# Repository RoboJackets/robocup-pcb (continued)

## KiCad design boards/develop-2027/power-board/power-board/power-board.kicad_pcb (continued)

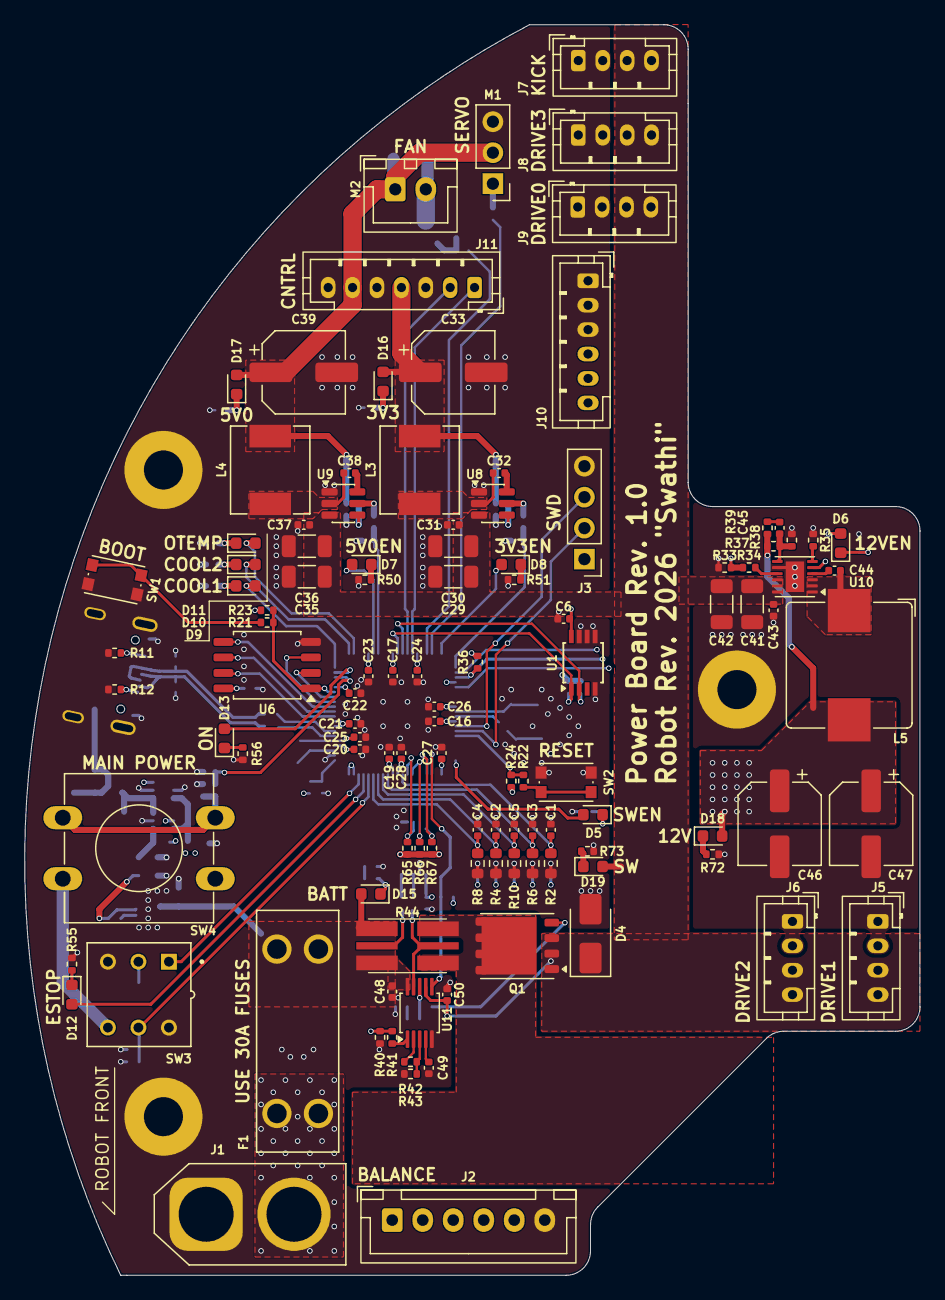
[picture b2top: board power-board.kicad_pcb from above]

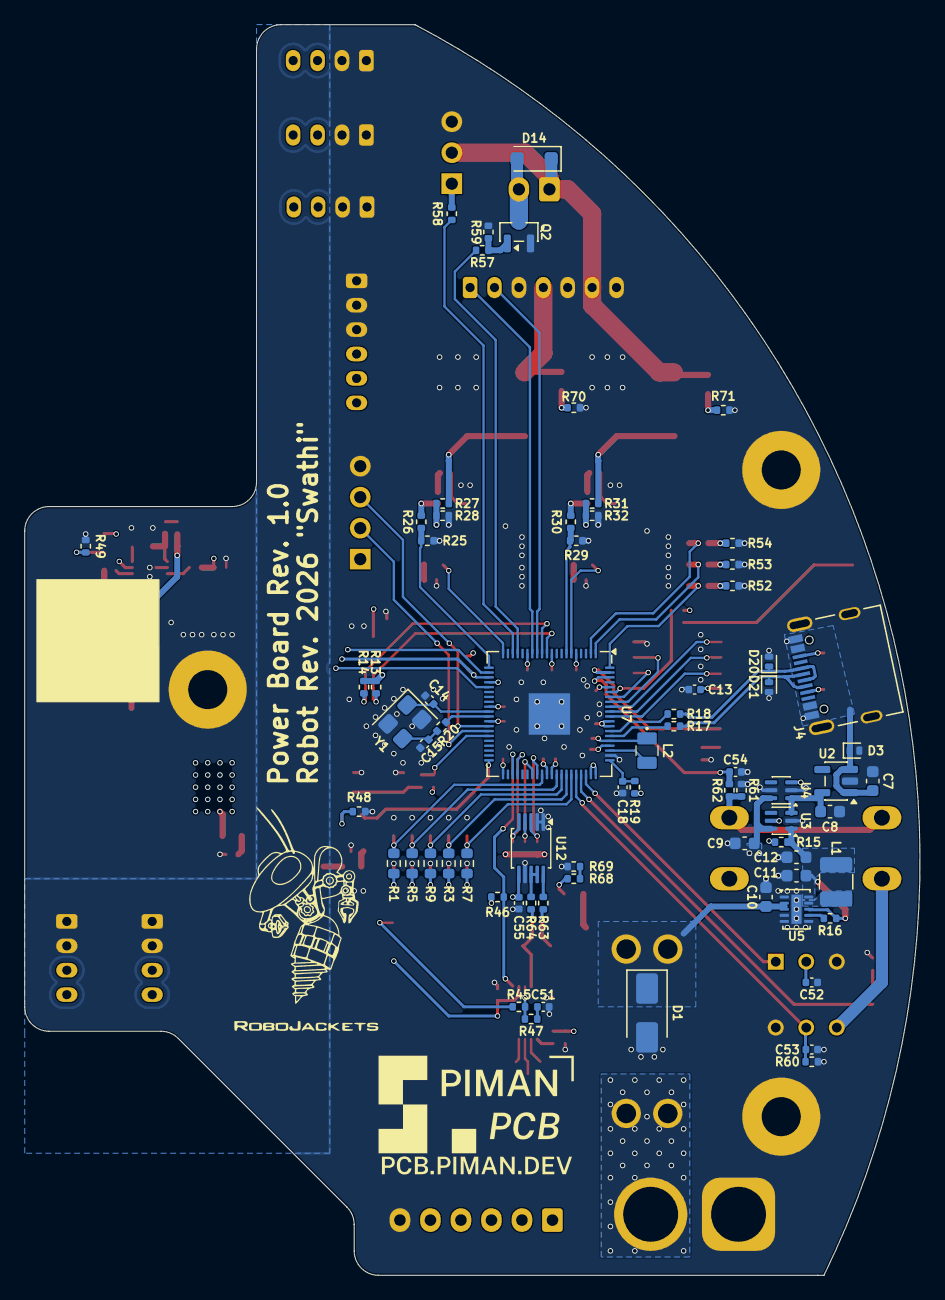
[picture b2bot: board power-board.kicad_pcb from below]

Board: 4 copper layers, 73.4 x 102.5 mm, 187 parts (72 on the bottom side), 119 nets.

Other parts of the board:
C6: 100n; C_0402_1005Metric
C48, C50: 100n 50V; C_0402_1005Metric
C49: 1n; C_0402_1005Metric
C51: 10n; C_0402_1005Metric
D4: SMAJ22CA; D_SMA
D19: KT-0603G; LED_0603_1608Metric
Q1: BSC014N06NS; Infineon_PG-TDSON-8_6.15x5.15mm
R13, R14, R73: 4.7k; R_0402_1005Metric
R40, R46: 100k; R_0402_1005Metric
R41, R47: 1k; R_0402_1005Metric
R42: 41.2k; R_0402_1005Metric
R43: 5.23k; R_0402_1005Metric
R44: 1.5m ± 1% 2W; R_Shunt_Analog_2512_6332_HighAccuracy
R45: 10; R_0402_1005Metric
U1: LM75ADP; TSSOP-8_3x3mm_P0.65mm
U11: TPS2491DGS; TSSOP-10_3x3mm_P0.5mm

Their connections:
+3.3V: C6.1, R13.1, R14.1, R46.1, U1.8 (VCC); also elsewhere on the board
/Battery Connectors/VBATT: C48.1, R44.4, U11.10 (VCC); also elsewhere on the board
/MCU/SCL0: R14.2, U1.2 (SCL); also elsewhere on the board
/MCU/SDA0: R13.2, U1.1 (SDA); also elsewhere on the board
/MCU/SW_OK: R46.2, U11.6 (PG); also elsewhere on the board
/Output Power Stage/25V, 30A Load Switch/SHUNT_H: R44.3; also elsewhere on the board
/Output Power Stage/25V, 30A Load Switch/SHUNT_L: R44.2, U11.9 (SENSE); also elsewhere on the board
/Output Power Stage/LOADSW_EN: R40.1, R41.2; also elsewhere on the board
GND: C6.2, C48.2, C49.2, C50.2, C51.2, D4.2 (A2), R40.2, R43.2, R73.2, U1.4 (GND), U1.5 (A2), U1.6 (A1), U1.7 (A0), U11.5 (GND); also elsewhere on the board
unnamed: C51.1, R47.2
unnamed: D19.1 (K), R73.1
unnamed: Q1.5 (D), R44.1
unnamed: Q1.4 (G), R45.1
unnamed: R41.1, U11.1 (EN)
unnamed: R45.2, R47.1, U11.8 (GATE)
unnamed: R42.2, R43.1, U11.3 (PROG)
unnamed: C49.1, U11.4 (TIMER)
unnamed: R42.1, U11.2 (VREF)
VIN: C50.1, D4.1 (A1), D19.2 (A), Q1.1 (S), Q1.2 (S), Q1.3 (S), U11.7 (OUT); also elsewhere on the board

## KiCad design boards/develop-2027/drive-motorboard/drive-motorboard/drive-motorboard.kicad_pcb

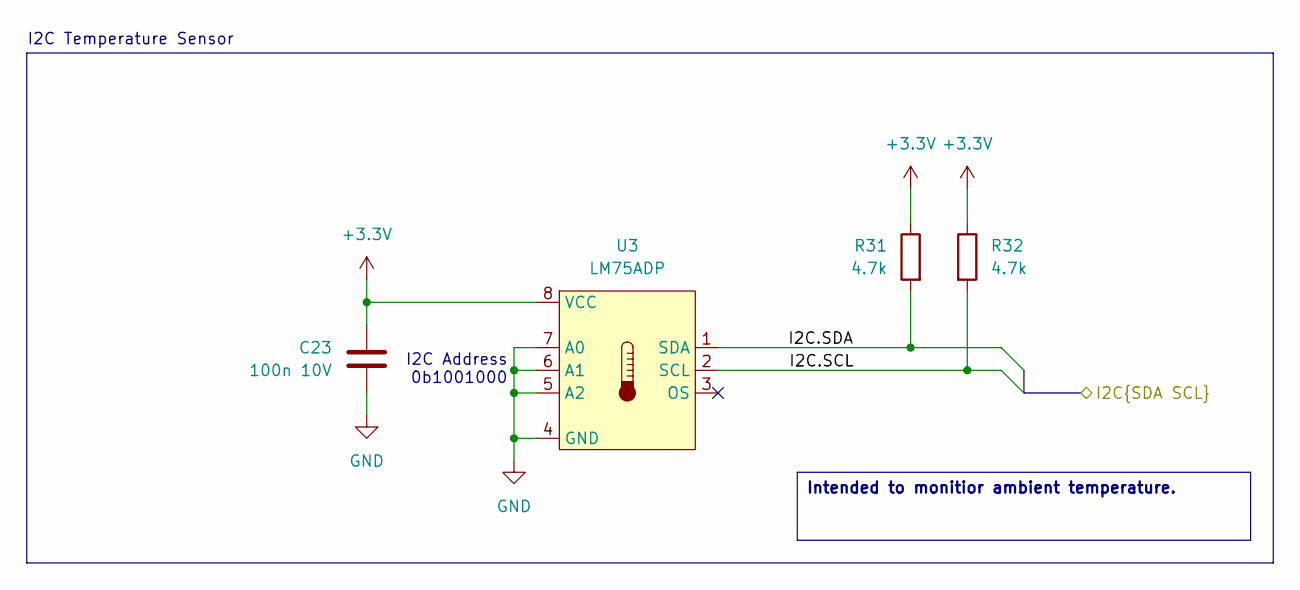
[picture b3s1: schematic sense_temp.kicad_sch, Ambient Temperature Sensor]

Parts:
C23: 100n 10V; C_0402_1005Metric; Manufacturer P/N CL05A104KA5NNNC
R31, R32: 4.7k; R_0402_1005Metric; Manufacturer P/N RC0402FR-074K7L
U3: LM75ADP; TSSOP-8_3x3mm_P0.65mm; Manufacturer P/N LM75ADP,118

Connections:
+3.3V: C23.1, R31.1, R32.1, U3.8 (VCC); also elsewhere on the board
/Motor Controller/I2C.SCL: R32.2, U3.2 (SCL); also elsewhere on the board
/Motor Controller/I2C.SDA: R31.2, U3.1 (SDA); also elsewhere on the board
GND: C23.2, U3.4 (GND), U3.5 (A2), U3.6 (A1), U3.7 (A0); also elsewhere on the board

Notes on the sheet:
I2C Address 0b1001000
I2C Temperature Sensor
Intended to monitior ambient temperature.

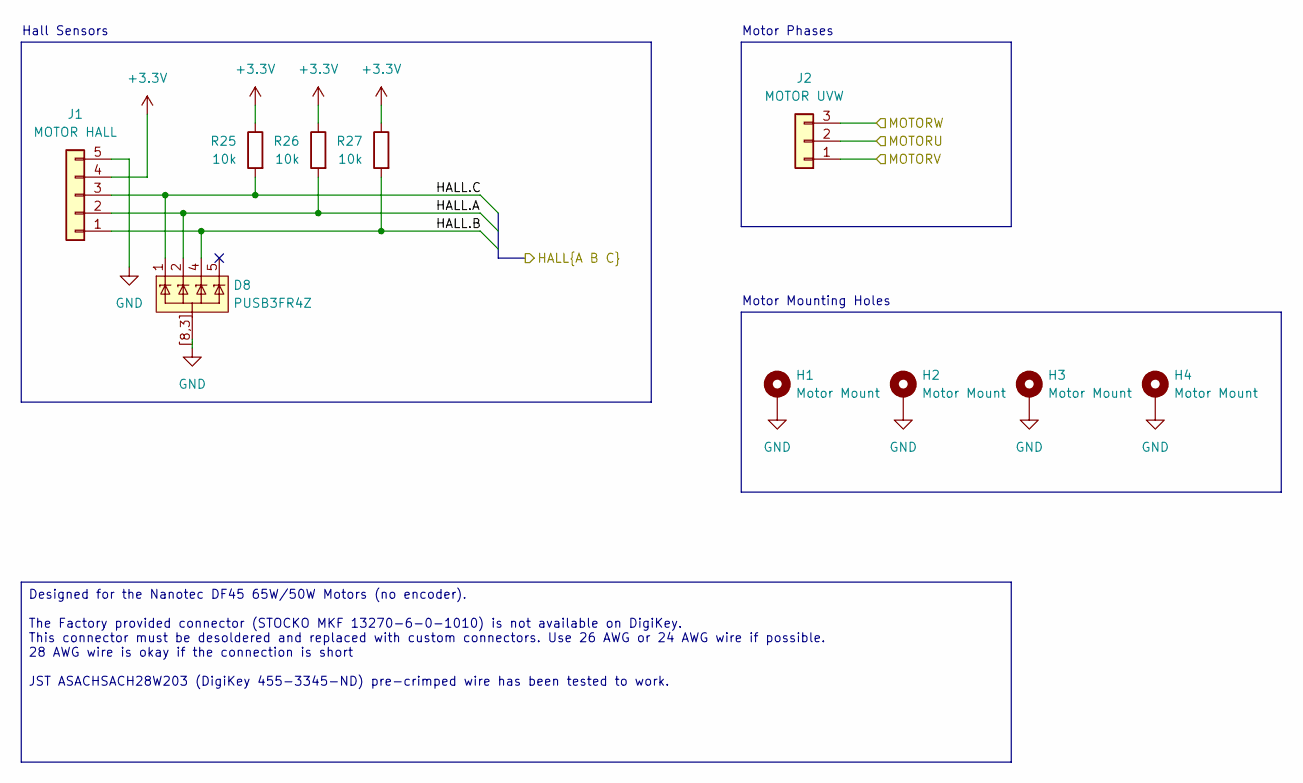
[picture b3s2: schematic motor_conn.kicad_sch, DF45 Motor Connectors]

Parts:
D8: PUSB3FR4Z; Diodes_UDFN-10_1x2.5mm_P0.5mm; Manufacturer P/N PUSB3FR4Z
H1: Motor Mount; MountingHole_3.2mm_M3_Pad; Manufacturer P/N H1
H2: Motor Mount; MountingHole_3.2mm_M3_Pad; Manufacturer P/N H2
H3: Motor Mount; MountingHole_3.2mm_M3_Pad; Manufacturer P/N H3
H4: Motor Mount; MountingHole_3.2mm_M3_Pad; Manufacturer P/N H4
J1: MOTOR HALL; JST_ACH_BM05B-ACHSS-A-GAN-ETF_1x05-1MP_P1.20mm_Vertical; Manufacturer P/N BM05B-ACHSS-A-GAN-ETF
J2: MOTOR UVW; JST_ACH_BM03B-ACHSS-GAN-ETF_1x03-1MP_P1.20mm_Vertical; Manufacturer P/N BM03B-ACHSS-GAN-TF
R25, R26, R27: 10k; R_0402_1005Metric; Manufacturer P/N RC0402FR-0710KL

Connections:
+3.3V: J1.4, R25.1, R26.1, R27.1; also elsewhere on the board
/Motor Connections/HALL.A: D8.2 (CH2), J1.2, R26.2; also elsewhere on the board
/Motor Connections/HALL.B: D8.4 (CH3), J1.1, R27.2; also elsewhere on the board
/Motor Connections/HALL.C: D8.1 (CH1), J1.3, R25.2; also elsewhere on the board
/Motor Connections/MOTORU: J2.2; also elsewhere on the board
/Motor Connections/MOTORV: J2.1; also elsewhere on the board
/Motor Connections/MOTORW: J2.3; also elsewhere on the board
GND: D8.3 (GND), D8.8 (GND), D8.[8,3] (GND), H1.1 (1_1), H2.1 (1_1), H3.1 (1_1), H4.1 (1_1), J1.5; also elsewhere on the board

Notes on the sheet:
Hall Sensors
Motor Phases
Motor Mounting Holes
Designed for the Nanotec DF45 65W/50W Motors (no encoder). The Factory provided connector (STOCKO MKF 13270-6-0-1010) is not available on DigiKey. This connector must be desoldered and replaced with custom connectors. Use 26 AWG or 24 AWG wire if possible. 28 AWG wire is okay if the connection is s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

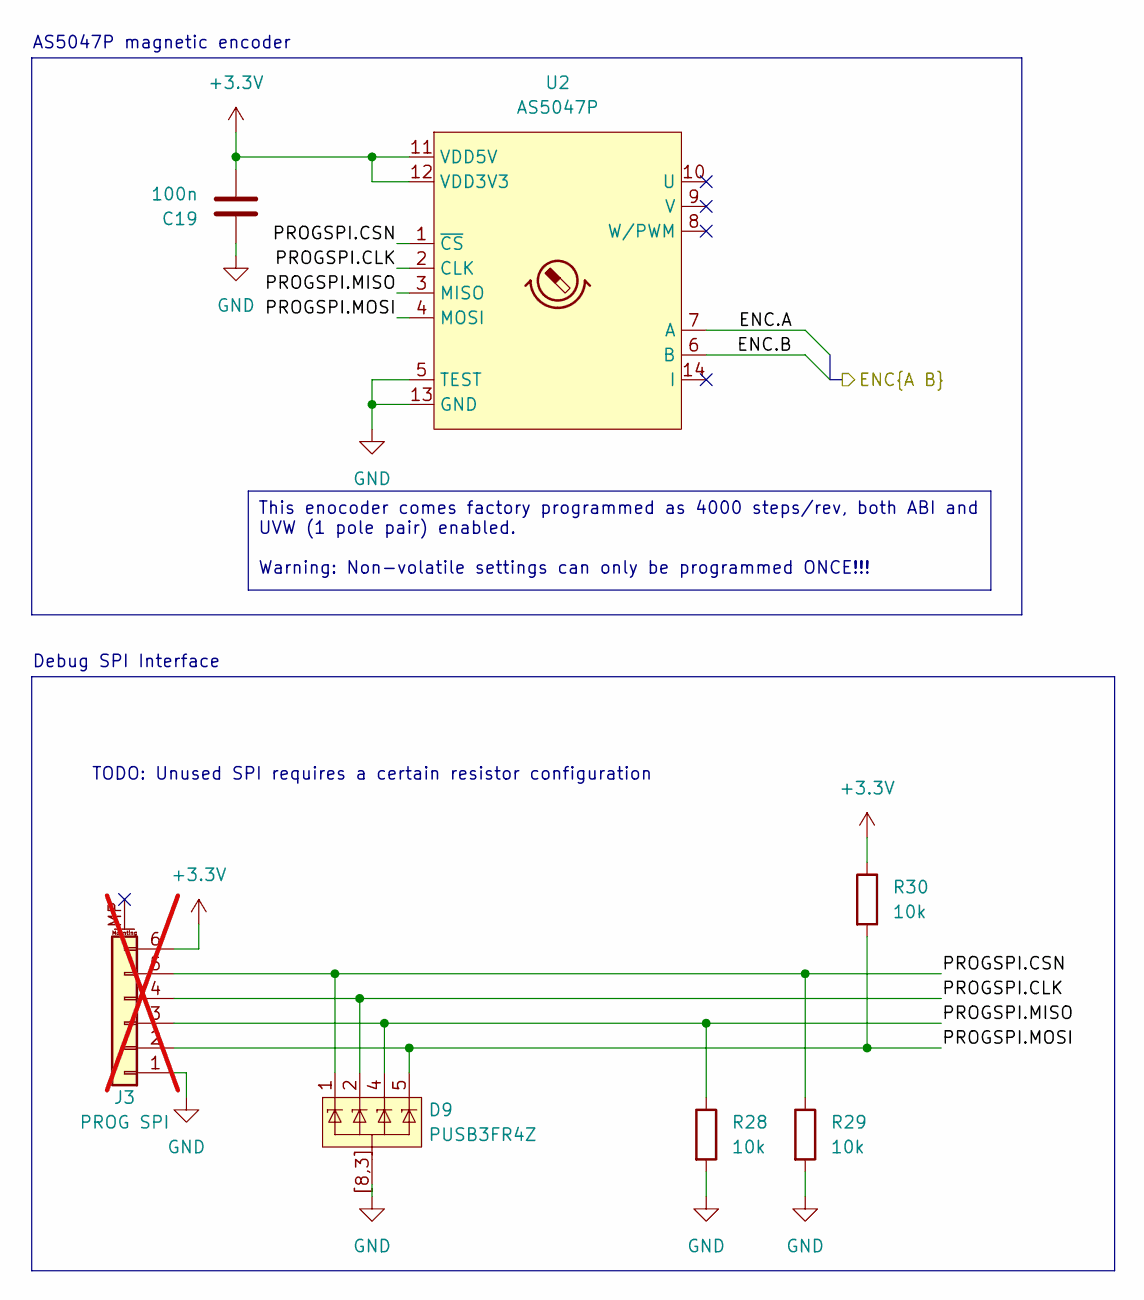
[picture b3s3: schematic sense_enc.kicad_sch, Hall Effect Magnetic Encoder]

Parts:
C19: 100n; C_0402_1005Metric; Manufacturer P/N CL05A104KA5NNNC
D9: PUSB3FR4Z; Diodes_UDFN-10_1x2.5mm_P0.5mm; Manufacturer P/N PUSB3FR4Z
J3: PROG SPI; JST_GH_SM06B-GHS-TB_1x06-1MP_P1.25mm_Horizontal; Manufacturer P/N SM06B-GHS-TB; not fitted
R28, R29, R30: 10k; R_0402_1005Metric; Manufacturer P/N RC0402FR-0710KL
U2: AS5047P; TSSOP-14_4.4x5mm_P0.65mm; Manufacturer P/N AS5047P

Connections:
+3.3V: C19.2, J3.6, R30.1, U2.11 (VDD5V), U2.12 (VDD3V3); also elsewhere on the board
/Magnetic Encoder/ENC.A: U2.7 (A); also elsewhere on the board
/Magnetic Encoder/ENC.B: U2.6 (B); also elsewhere on the board
/Magnetic Encoder/PROGSPI.CLK: D9.2 (CH2), J3.4, U2.2 (CLK)
/Magnetic Encoder/PROGSPI.CSN: D9.1 (CH1), J3.5, R29.1, U2.1 (~CS)
/Magnetic Encoder/PROGSPI.MISO: D9.4 (CH3), J3.3, R28.1, U2.3 (MISO)
/Magnetic Encoder/PROGSPI.MOSI: D9.5 (CH4), J3.2, R30.2, U2.4 (MOSI)
GND: C19.1, D9.3 (GND), D9.8 (GND), D9.[8,3] (GND), J3.1, R28.2, R29.2, U2.5 (TEST), U2.13 (GND); also elsewhere on the board

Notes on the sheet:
TODO: Unused SPI requires a certain resistor configuration
Debug SPI Interface
AS5047P magnetic encoder
This enocoder comes factory programmed as 4000 steps/rev, both ABI and UVW (1 pole pair) enabled. Warning: Non-volatile settings can only be programmed ONCE!!!

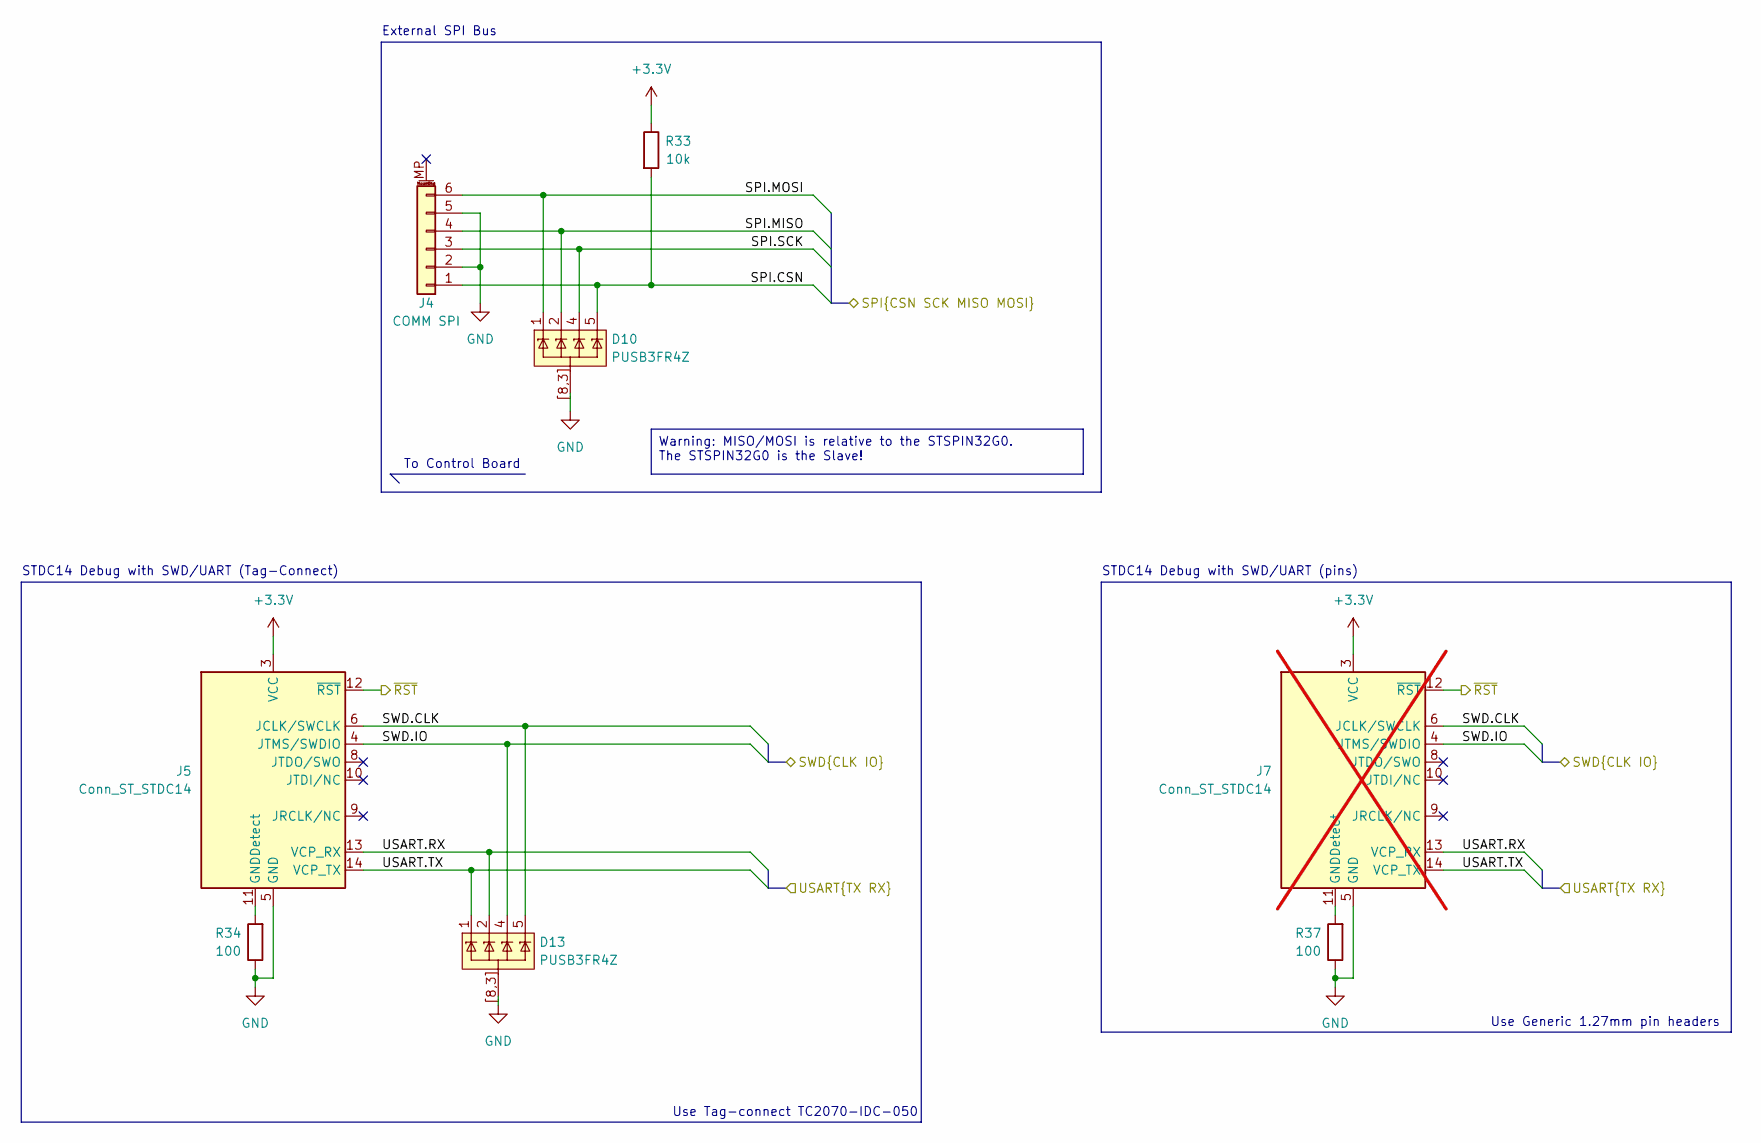
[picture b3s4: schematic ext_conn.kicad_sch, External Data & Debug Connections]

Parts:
D10, D13: PUSB3FR4Z; Diodes_UDFN-10_1x2.5mm_P0.5mm; Manufacturer P/N PUSB3FR4Z
J4: COMM SPI; JST_GH_SM06B-GHS-TB_1x06-1MP_P1.25mm_Horizontal; Manufacturer P/N SM06B-GHS-TB
J5: Conn_ST_STDC14; Tag-Connect_TC2070-IDC-FP_2x07_P1.27mm_Vertical; Manufacturer P/N J5
J7: Conn_ST_STDC14; PinHeader_2x07_P1.27mm_Vertical_SMD; Manufacturer P/N FTSH-107-01-L-DV-K; not fitted
R33: 10k; R_0402_1005Metric; Manufacturer P/N RC0402FR-0710KL
R34, R37: 100; R_0402_1005Metric; Manufacturer P/N RC0402FR-07100RL

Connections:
+3.3V: J5.3 (VCC), J7.3 (VCC), R33.1; also elsewhere on the board
/External Connections/SPI.CSN: D10.5 (CH4), J4.1, R33.2; also elsewhere on the board
/External Connections/SPI.MISO: D10.2 (CH2), J4.4; also elsewhere on the board
/External Connections/SPI.MOSI: D10.1 (CH1), J4.6; also elsewhere on the board
/External Connections/SPI.SCK: D10.4 (CH3), J4.3; also elsewhere on the board
/External Connections/SWD.CLK: D13.5 (CH4), J5.6 (JCLK/SWCLK), J7.6 (JCLK/SWCLK); also elsewhere on the board
/External Connections/SWD.IO: D13.4 (CH3), J5.4 (JTMS/SWDIO), J7.4 (JTMS/SWDIO); also elsewhere on the board
/External Connections/USART.RX: D13.2 (CH2), J5.13 (VCP_RX), J7.13 (VCP_RX); also elsewhere on the board
/External Connections/USART.TX: D13.1 (CH1), J5.14 (VCP_TX), J7.14 (VCP_TX); also elsewhere on the board
/External Connections/~RST: J5.12 (~RST), J7.12 (~RST); also elsewhere on the board
GND: D10.3 (GND), D10.8 (GND), D10.[8,3] (GND), D13.3 (GND), D13.8 (GND), D13.[8,3] (GND), J4.2, J4.5, J5.5 (GND), J5.7 (GND), J7.5 (GND), J7.7 (GND), R34.1, R37.1; also elsewhere on the board
unnamed: J5.11 (GNDDetect), R34.2
unnamed: J7.11 (GNDDetect), R37.2

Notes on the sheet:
External SPI Bus
To Control Board
STDC14 Debug with SWD/UART (pins)
STDC14 Debug with SWD/UART (Tag-Connect)
Use Generic 1.27mm pin headers
Use Tag-connect TC2070-IDC-050
Warning: MISO/MOSI is relative to the STSPIN32G0. The STSPIN32G0 is the Slave!

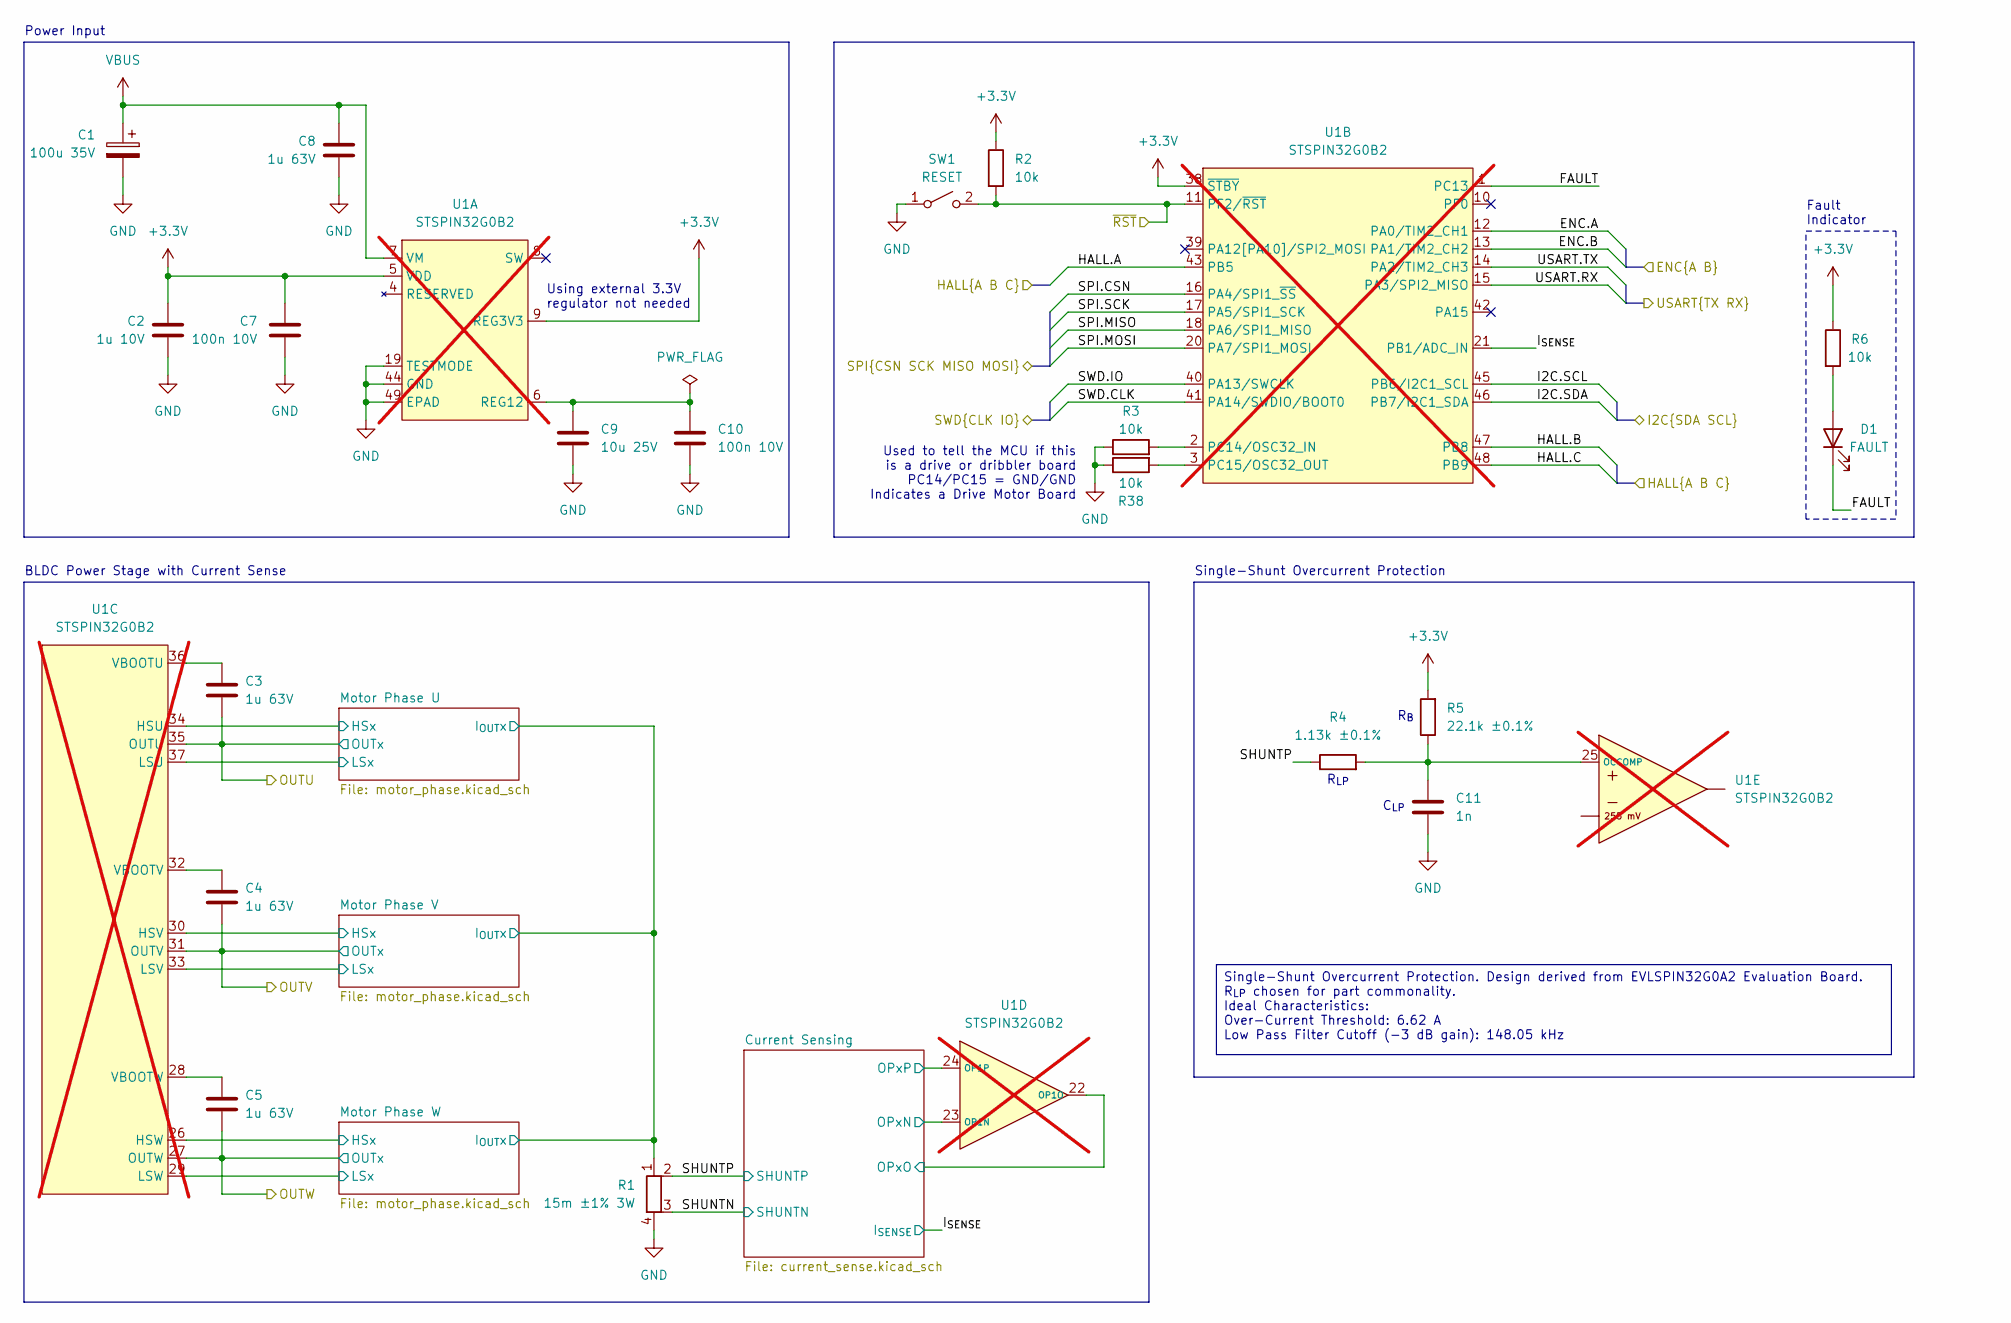
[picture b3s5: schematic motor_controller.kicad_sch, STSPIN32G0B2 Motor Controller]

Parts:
C1: 100u 35V; C_Elec_6.3x5.8; Manufacturer P/N EEE-FT1V101AP
C2: 1u 10V; C_0603_1608Metric; Manufacturer P/N CL10B105KB8NQNC
C3, C4, C5, C8: 1u 63V; C_0603_1608Metric; Manufacturer P/N CL10B105KB8NQNC
C7, C10: 100n 10V; C_0402_1005Metric; Manufacturer P/N CL05A104KA5NNNC
C9: 10u 25V; C_0603_1608Metric; Manufacturer P/N GRM188R6YA106MA73D
C11: 1n; C_0402_1005Metric; Manufacturer P/N CL05B102KB5NNNC
D1: FAULT; LED_0603_1608Metric; Manufacturer P/N LTST-C190KRKT
R1: 15m ±1% 3W; R_Shunt_Analog_2512_6332_HighAccuracy; Manufacturer P/N CRA2512-FZ-R015ELF
R2, R3, R6, R38: 10k; R_0402_1005Metric; Manufacturer P/N RC0402FR-0710KL
R4: 1.13k ±0.1%; R_0402_1005Metric; Manufacturer P/N RT0402BRD071K13L
R5: 22.1k ±0.1%; R_0402_1005Metric; Manufacturer P/N PTFR0402B22K1P9
SW1: RESET; SW_Push_1P1T_NO_CK_KMR2; Manufacturer P/N KMR221NGLFS
U1: STSPIN32G0B2; VQFN-48-1EP_7x7mm_P0.5mm_EP2.6x2.6mm; Manufacturer P/N STSPIN32G0B2; not fitted

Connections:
+3.3V: C2.1, C7.1, R2.1, R5.2, R6.1, U1.5 (VDD), U1.9 (REG3V3), U1.38 (~STBY); also elsewhere on the board
/External Connections/SPI.CSN: U1.16 (PA4/SPI1_~SS); also elsewhere on the board
/External Connections/SPI.MISO: U1.18 (PA6/SPI1_MISO); also elsewhere on the board
/External Connections/SPI.MOSI: U1.20 (PA7/SPI1_MOSI); also elsewhere on the board
/External Connections/SPI.SCK: U1.17 (PA5/SPI1_SCK); also elsewhere on the board
/External Connections/SWD.CLK: U1.41 (PA14/SWDIO/BOOT0); also elsewhere on the board
/External Connections/SWD.IO: U1.40 (PA13/SWCLK); also elsewhere on the board
/External Connections/USART.RX: U1.15 (PA3/SPI2_MISO); also elsewhere on the board
/External Connections/USART.TX: U1.14 (PA2/TIM2_CH3); also elsewhere on the board
/External Connections/~RST: R2.2, SW1.2 (B), U1.11 (PF2/~RST); also elsewhere on the board
/Magnetic Encoder/ENC.A: U1.12 (PA0/TIM2_CH1); also elsewhere on the board
/Magnetic Encoder/ENC.B: U1.13 (PA1/TIM2_CH2); also elsewhere on the board
/Motor Connections/HALL.A: U1.43 (PB5); also elsewhere on the board
/Motor Connections/HALL.B: U1.47 (PB8); also elsewhere on the board
/Motor Connections/HALL.C: U1.48 (PB9); also elsewhere on the board
/Motor Connections/MOTORU: C3.2, U1.35 (OUTU); also elsewhere on the board
/Motor Connections/MOTORV: C4.2, U1.31 (OUTV); also elsewhere on the board
/Motor Connections/MOTORW: C5.2, U1.27 (OUTW); also elsewhere on the board
/Motor Controller/Current Sensing/OPxN: U1.23 (OP1N); also elsewhere on the board
/Motor Controller/Current Sensing/OPxO: U1.22 (OP1O); also elsewhere on the board
/Motor Controller/Current Sensing/OPxP: U1.24 (OP1P); also elsewhere on the board
/Motor Controller/FAULT: D1.1 (K), U1.1 (PC13)
/Motor Controller/I2C.SCL: U1.45 (PB6/I2C1_SCL); also elsewhere on the board
/Motor Controller/I2C.SDA: U1.46 (PB7/I2C1_SDA); also elsewhere on the board
/Motor Controller/I_{SENSE}: U1.21 (PB1/ADC_IN); also elsewhere on the board
/Motor Controller/Motor Phase U/HSx: U1.34 (HSU); also elsewhere on the board
/Motor Controller/Motor Phase U/I_{OUT}x: R1.1; also elsewhere on the board
/Motor Controller/Motor Phase U/LSx: U1.37 (LSU); also elsewhere on the board
/Motor Controller/Motor Phase V/HSx: U1.30 (HSV); also elsewhere on the board
/Motor Controller/Motor Phase V/LSx: U1.33 (LSV); also elsewhere on the board
/Motor Controller/Motor Phase W/HSx: U1.26 (HSW); also elsewhere on the board
/Motor Controller/Motor Phase W/LSx: U1.29 (LSW); also elsewhere on the board
/Motor Controller/SHUNTN: R1.3; also elsewhere on the board
/Motor Controller/SHUNTP: R1.2, R4.1; also elsewhere on the board
GND: C1.2, C2.2, C7.2, C8.2, C9.2, C10.2, C11.2, R1.4, R3.1, R38.1, SW1.1 (A), U1.19 (TESTMODE), U1.44 (GND), U1.49 (EPAD); also elsewhere on the board
unnamed: D1.2 (A), R6.2
unnamed: C3.1, U1.36 (VBOOTU)
unnamed: C4.1, U1.32 (VBOOTV)
unnamed: C5.1, U1.28 (VBOOTW)
unnamed: R3.2, U1.2 (PC14/OSC32_IN)
unnamed: R38.2, U1.3 (PC15/OSC32_OUT)
unnamed: C11.1, R4.2, R5.1, U1.25 (OCCOMP)
unnamed: C9.1, C10.1, U1.6 (REG12)
VBUS: C1.1, C8.1, U1.7 (VM); also elsewhere on the board

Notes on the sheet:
BLDC Power Stage with Current Sense
Fault Indicator
Power Input
R_{LP}
Single-Shunt Overcurrent Protection
C_{LP}
Used to tell the MCU if this is a drive or dribbler board PC14/PC15 = GND/GND Indicates a Drive Motor Board
R_{B}
Using external 3.3V regulator not needed
Single-Shunt Overcurrent Protection. Design derived from EVLSPIN32G0A2 Evaluation Board. R_{LP} chosen for part commonality. Ideal Characteristics: Over-Current Threshold: 6.62 A Low Pass Filter Cutoff (-3 dB gain): 148.05 kHz

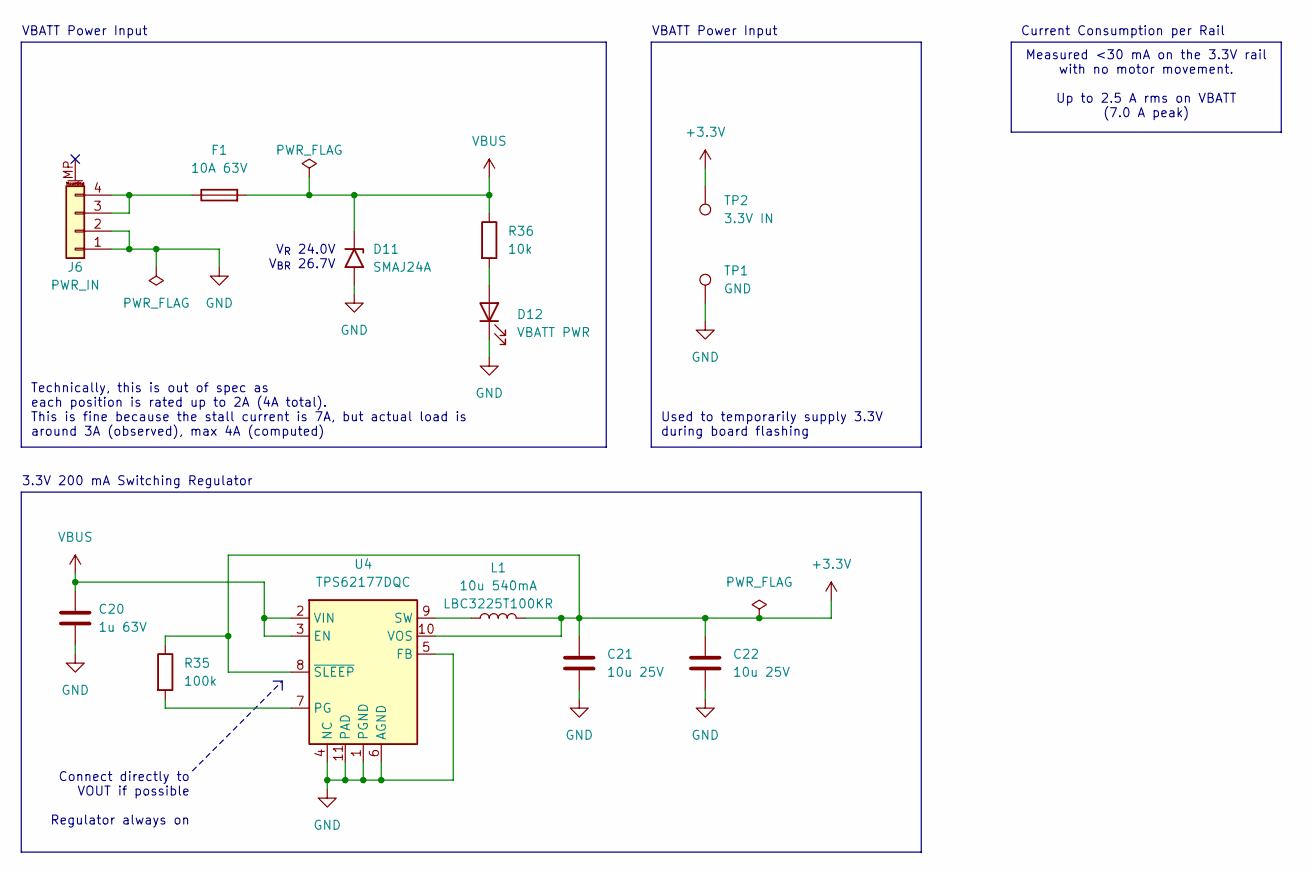
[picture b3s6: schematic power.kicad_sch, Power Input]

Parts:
C20: 1u 63V; C_0603_1608Metric; Manufacturer P/N CL10B105KB8NQNC
C21, C22: 10u 25V; C_0603_1608Metric; Manufacturer P/N GRM188R6YA106MA73D
D11: SMAJ24A; D_SMA; Manufacturer P/N SMAJ24A
D12: VBATT PWR; LED_0603_1608Metric; Manufacturer P/N LTST-C190KGKT
F1: 10A 63V; Fuse_1206_3216Metric_Pad1.42x1.75mm_HandSolder; Manufacturer P/N 3413.0328.22
J6: PWR_IN; JST_PH_S4B-PH-SM4-TB_1x04-1MP_P2.00mm_Horizontal; Manufacturer P/N S4B-PH-SM4-TB
L1: 10u 540mA; L_1210_3225Metric; Manufacturer P/N LBC3225T100KR
R35: 100k; R_0402_1005Metric; Manufacturer P/N RC0402FR-07100KL
R36: 10k; R_0402_1005Metric; Manufacturer P/N RC0402FR-0710KL
TP1: GND; TestPoint_Pad_2.0x2.0mm
TP2: 3.3V IN; TestPoint_Pad_2.0x2.0mm
U4: TPS62177DQC; WSON-10-1EP_2x3mm_P0.5mm_EP0.84x2.4mm; Manufacturer P/N TPS62177DQC

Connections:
+3.3V: C21.1, C22.1, L1.2, R35.1, TP2.1 (1_1), U4.8 (~SLEEP), U4.10 (VOS); also elsewhere on the board
GND: C20.2, C21.2, C22.2, D11.2 (A2), D12.1 (K), J6.1, J6.2, TP1.1 (1_1), U4.1 (PGND), U4.4 (NC), U4.5 (FB), U4.6 (AGND), U4.11 (PAD); also elsewhere on the board
unnamed: D12.2 (A), R36.2
unnamed: F1.1, J6.3, J6.4
unnamed: R35.2, U4.7 (PG)
unnamed: L1.1, U4.9 (SW)
VBUS: C20.1, D11.1 (A1), F1.2, R36.1, U4.2 (VIN), U4.3 (EN); also elsewhere on the board

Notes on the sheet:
Used to temporarily supply 3.3V during board flashing
3.3V 200 mA Switching Regulator
VBATT Power Input
Measured <30 mA on the 3.3V rail with no motor movement. Up to 2.5 A rms on VBATT (7.0 A peak)
V_{R} 24.0V V_{BR} 26.7V
Technically, this is out of spec as each position is rated up to 2A (4A total). This is fine because the stall current is 7A, but actual load is around 3A (observed), max 4A (computed)
Current Consumption per Rail
Connect directly to VOUT if possible Regulator always on

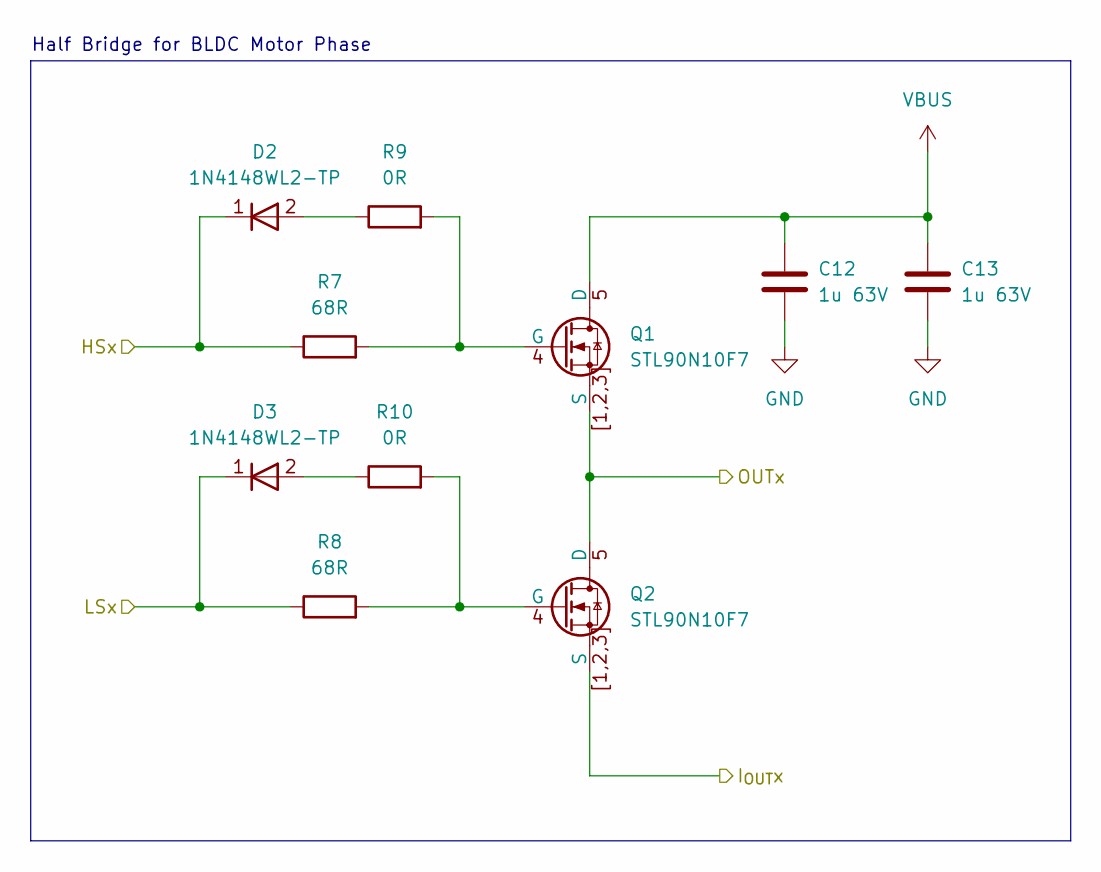
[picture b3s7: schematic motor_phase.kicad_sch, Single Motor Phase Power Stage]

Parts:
C12, C13: 1u 63V; C_0603_1608Metric; Manufacturer P/N CL10B105KB8NQNC
D2, D3: 1N4148WL2-TP; D_SOD-882; Manufacturer P/N 1N4148WL2-TP
Q1, Q2: STL90N10F7; PQFN-8-EP_6x5mm_P1.27mm_Generic; Manufacturer P/N STL90N10F7
R7, R8: 68R; R_0402_1005Metric; Manufacturer P/N RC0402FR-0768RL
R9, R10: 0R; R_0402_1005Metric; Manufacturer P/N RC0402JR-070RL

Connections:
/Motor Connections/MOTORU: Q1.1 (S), Q1.2 (S), Q1.3 (S), Q1.[1,2,3] (S), Q2.5 (D); also elsewhere on the board
/Motor Controller/Motor Phase U/HSx: D2.1 (K), R7.1; also elsewhere on the board
/Motor Controller/Motor Phase U/I_{OUT}x: Q2.1 (S), Q2.2 (S), Q2.3 (S); also elsewhere on the board
/Motor Controller/Motor Phase U/LSx: D3.1 (K), R8.1; also elsewhere on the board
GND: C12.2, C13.2; also elsewhere on the board
unnamed: D2.2 (A), R9.1
unnamed: D3.2 (A), R10.1
unnamed: Q1.4 (G), R7.2, R9.2
unnamed: Q2.4 (G), R8.2, R10.2
VBUS: C12.1, C13.1, Q1.5 (D); also elsewhere on the board

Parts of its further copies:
C14, C15, C16, C17: 1u 63V; C_0603_1608Metric; Manufacturer P/N CL10B105KB8NQNC
D4, D5, D6, D7: 1N4148WL2-TP; D_SOD-882; Manufacturer P/N 1N4148WL2-TP
Q3, Q4, Q5, Q6: STL90N10F7; PQFN-8-EP_6x5mm_P1.27mm_Generic; Manufacturer P/N STL90N10F7
R11, R12, R15, R16: 68R; R_0402_1005Metric; Manufacturer P/N RC0402FR-0768RL
R13, R14, R17, R18: 0R; R_0402_1005Metric; Manufacturer P/N RC0402JR-070RL

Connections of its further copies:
/Motor Connections/MOTORV: Q3.1 (S), Q3.2 (S), Q3.3 (S), Q4.5 (D); also elsewhere on the board
/Motor Connections/MOTORW: Q5.1 (S), Q5.2 (S), Q5.3 (S), Q6.5 (D); also elsewhere on the board
/Motor Controller/Motor Phase U/I_{OUT}x: Q4.1 (S), Q4.2 (S), Q4.3 (S), Q6.1 (S), Q6.2 (S), Q6.3 (S); also elsewhere on the board
/Motor Controller/Motor Phase V/HSx: D4.1 (K), R11.1; also elsewhere on the board
/Motor Controller/Motor Phase V/LSx: D5.1 (K), R12.1; also elsewhere on the board
/Motor Controller/Motor Phase W/HSx: D6.1 (K), R15.1; also elsewhere on the board
/Motor Controller/Motor Phase W/LSx: D7.1 (K), R16.1; also elsewhere on the board
GND: C14.2, C15.2, C16.2, C17.2; also elsewhere on the board
unnamed: D4.2 (A), R13.1
unnamed: D5.2 (A), R14.1
unnamed: D6.2 (A), R17.1
unnamed: D7.2 (A), R18.1
unnamed: Q3.4 (G), R11.2, R13.2
unnamed: Q4.4 (G), R12.2, R14.2
unnamed: Q5.4 (G), R15.2, R17.2
unnamed: Q6.4 (G), R16.2, R18.2
VBUS: C14.1, C15.1, C16.1, C17.1, Q3.5 (D), Q5.5 (D); also elsewhere on the board

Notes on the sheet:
Half Bridge for BLDC Motor Phase
